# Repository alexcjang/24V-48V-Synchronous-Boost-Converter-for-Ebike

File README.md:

# 24V-48V Synchronous Boost Converter for Ebike

# Synchronous Boost Converter

24V→48V DC-DC converter, 250W rated, 97.51% peak efficiency.

🏆 Won "Most Efficient Design" across all teams in Fall '25 class of Power Electronics Lab.

## Overview
Boost converter designed to power 3 phase electric bike motor, which required conversion from 24-48V. Our team optimized efficiency, winning the category, at the cost of size. This was designed for the Fall '25 class of Power Electronics Lab.

## Key Results
- Peak efficiency: 97.51% at 250W.
- Output ripple: 0.905V
- Efficiency across load range:

## Design
- **Topology:** Synchronous Boost for high efficiency
- **Magnetics:** Custom-wound inductor — 92.16µH, 19 turns, 0.79mm gap, 10 AWG. These specs were chosen using the Kg method on the E cores that were available in the lab, as well as to achieve Vin = 24V, Vout = 48V, ripple = 0.125, and inductor I = 10.417A.
- **Control:** Register-level PWM with dead-time management on TI C2000,
  ADC-based current/voltage sensing
- **PCB:** 4-layer, minimized gating loops and cut ground planes to reduce parasitic capacitance and inductance, seperated sensitive ADC/control signals from high di/dt and high dv/dt areas

## What I'd Change
I would love to have optimized the dead time and switching a bit more. With precise switching, we could have achieved zero voltage switching consistently, which would removes the switching loss from that cycle. We did not have the time to implement this, and also decided that it was too risky as choosing the wrong dead time could result in a short circuit of the switching loop and fry our MOSFETs. If I were to take on this project again outside of the class constraints, I would try different types of cores to allow for a larger inductor which could further increase efficiency and reduce ripple.

## Media

Board 3D model
<br><br><br>

Peak Efficiency Oscilloscope Capture

## Tools
LTSpice, MATLAB, KiCad, TI C2000 (C)

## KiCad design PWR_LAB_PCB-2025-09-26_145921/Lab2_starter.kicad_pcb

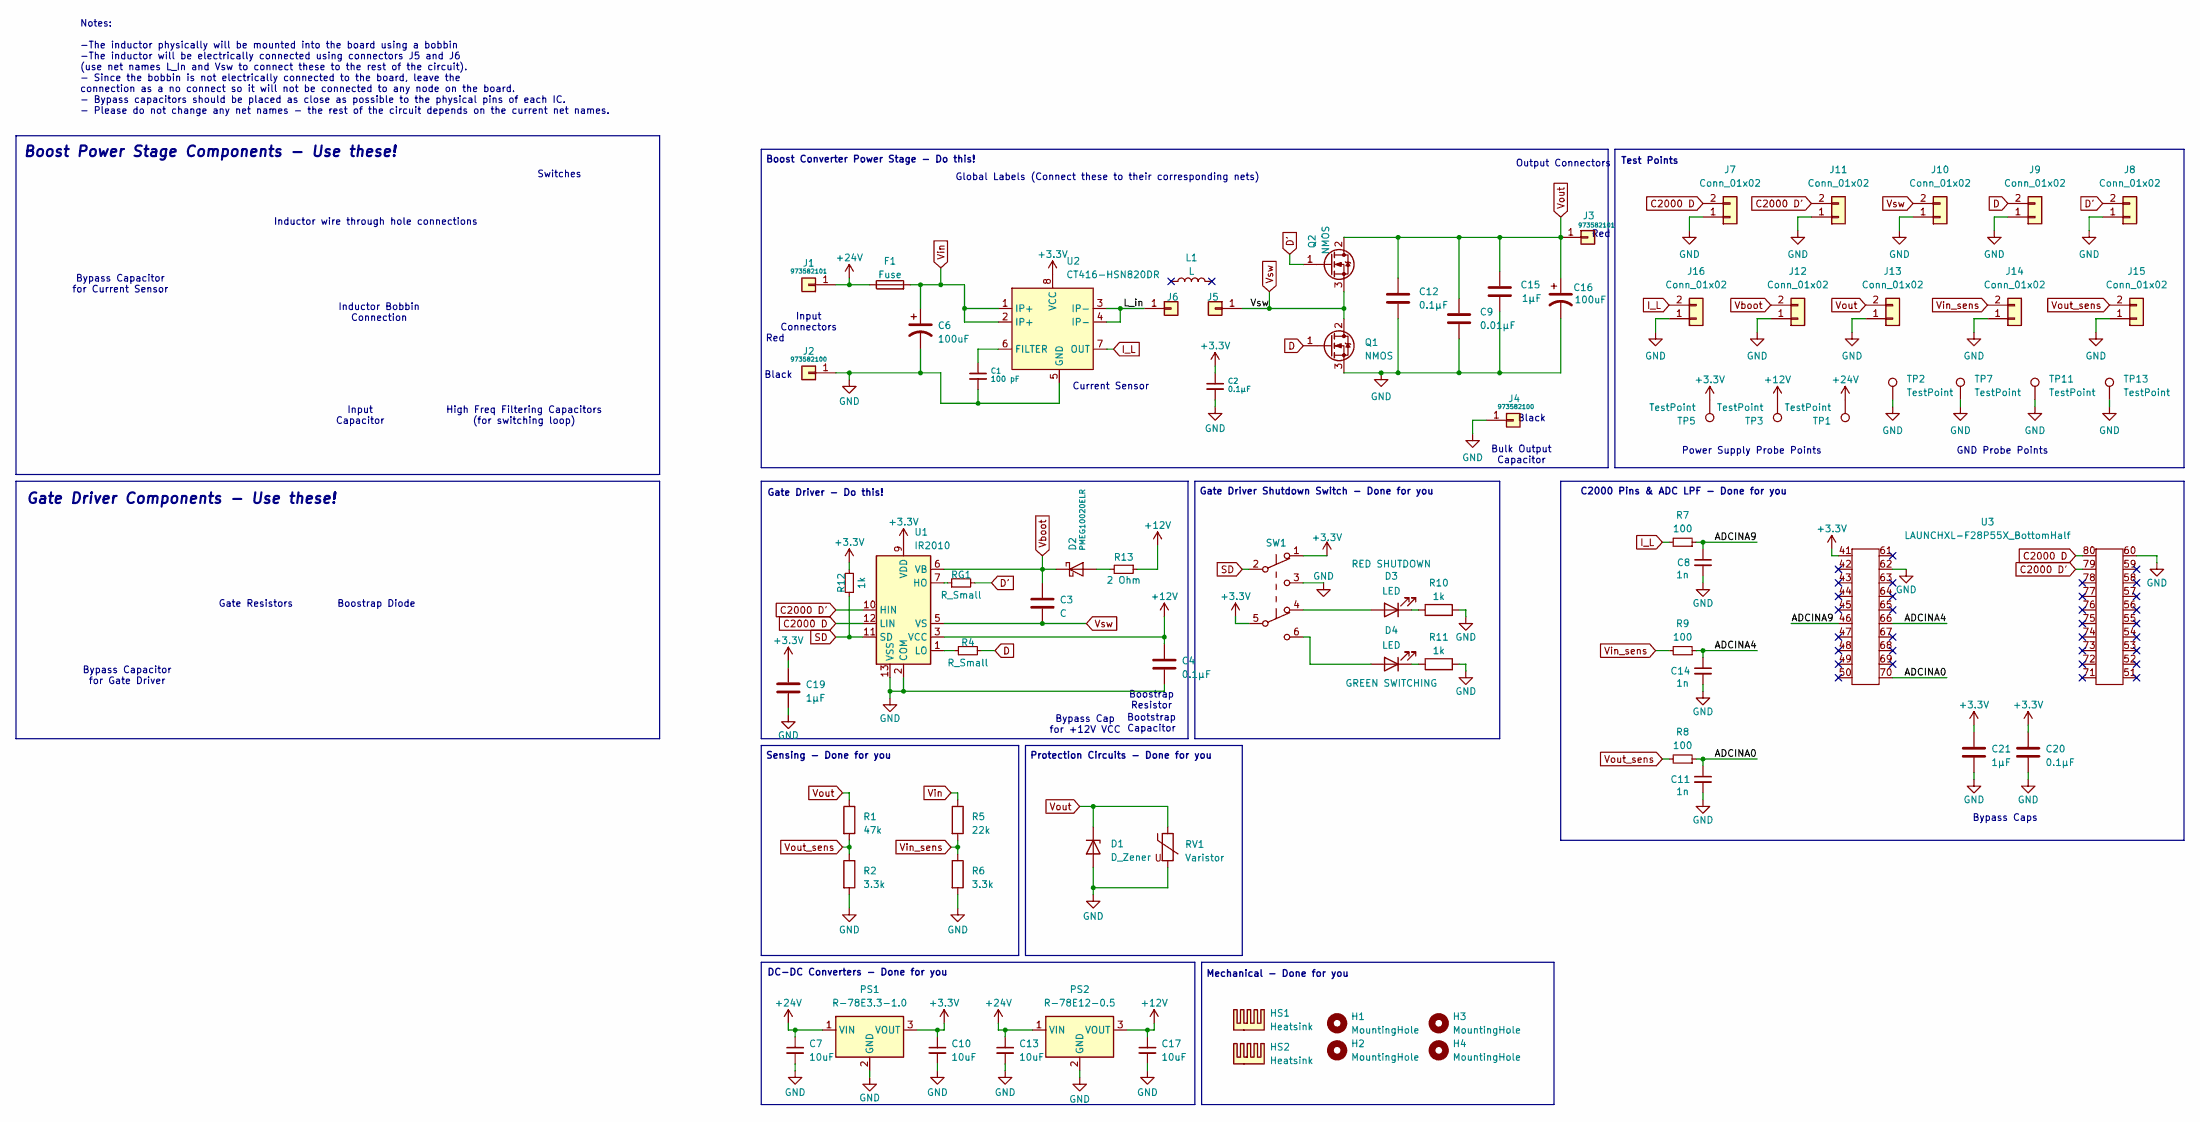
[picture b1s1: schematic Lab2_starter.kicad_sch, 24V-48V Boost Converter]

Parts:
C1: 100 pF; C_0805_2012Metric
C2, C4, C12, C20: 0.1μF; C_0805_2012Metric
C3: C; C_0805_2012Metric
C6, C16: 100uF; 16PX2200MEFC10X20
C7, C10, C13, C17: 10uF; C_0805_2012Metric
C8, C11, C14: 1n; C_0805_2012Metric
C9: 0.01μF; C_0805_2012Metric
C15, C19, C21: 1μF; C_0805_2012Metric
D1: D_Zener; 1.5KE75A
D2: PMEG10020ELR; Nexperia_CFP3_SOD-123W
D3, D4: LED; WL-SMRW_1206_REC
F1: Fuse; 696108003002
H1, H2, H3, H4: MountingHole; MountingHole_3.2mm_M3
HS1, HS2: Heatsink; HSS-B20-NPS-01
J1, J3: 973582101
J2, J4: 973582100
J5, J6: Conn_01x01; Inductor_wire_conn
J7, J8, J9, J10, J11, J12, J13, J14, J15, J16: Conn_01x02; TP
L1: L; Inductor
PS1: R-78E3.3-1.0; PARTREV 6
PS2: R-78E12-0.5; R-78E-0.5_RCP
Q1, Q2: NMOS; TO-220-3_Vertical
R1: 47k; R_0805_2012Metric
R2, R6: 3.3k; R_0805_2012Metric
R4: R_Small; R_0805_2012Metric
R5: 22k; R_0805_2012Metric
R7, R8, R9: 100; R_0805_2012Metric
R10, R11, R12: 1k; R_0805_2012Metric
R13: 2 Ohm; R_0805_2012Metric
RG1: R_Small; R_0805_2012Metric
RV1: Varistor; V100ZA15P
SW1: SW_Push_DPDT; SLW1116297AD
TP1, TP2, TP3, TP5, TP7, TP11, TP13: TestPoint; TestPoint_Loop_D1.80mm_Drill1.0mm_Beaded
U1: IR2010; 1-2199298-3
U2: CT416-HSN820DR; SOIC-8_3.9x4.9mm_P1.27mm
U3: LAUNCHXL-F28P55X_BottomHalf

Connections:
+3.3V: C2.1, C10.1, C19.1, C20.1, C21.1, PS1.3 (VOUT), R12.2, SW1.1 (A), SW1.5 (B), TP5.1, U1.9 (VDD), U2.8 (VCC), U3.41
+12V: C4.1, C17.1, PS2.3 (VOUT), R13.1, TP3.1, U1.3 (VCC)
+24V: C7.1, C13.1, F1.1, J1.1, PS1.1 (VIN), PS2.1 (VIN), TP1.1
/ADCINA0: C11.1, R8.1, U3.70
/ADCINA4: C14.1, R9.1, U3.66
/ADCINA9: C8.1, R7.1, U3.46
/L_in: J6.1, U2.3 (IP-), U2.4 (IP-)
C2000 D: J7.2, U1.12 (LIN), U3.80
C2000 D': J11.2, U1.10 (HIN), U3.79
D: J9.2, Q1.1 (G), R4.2
D': J8.2, Q2.1 (G), RG1.2
GND: C1.2, C2.2, C4.2, C6.2, C7.2, C8.2, C9.2, C10.2, C11.2, C12.2, C13.2, C14.2, C15.2, C16.2, C17.2, C19.2, C20.2, C21.2, D1.2 (A), J2.1, J4.1, J7.1, J8.1, J9.1, J10.1, J11.1, J12.1, J13.1, J14.1, J15.1, J16.1, PS1.2 (GND), PS2.2 (GND), Q1.3 (S), R2.2, R6.2, R10.2, R11.2, RV1.2, SW1.3 (C), TP2.1, TP7.1, TP11.1, TP13.1, U1.2 (COM), U1.13 (VSS), U2.5 (GND), U3.60, U3.62
I_L: J16.2, R7.2, U2.7 (OUT)
unnamed: D2.2 (A), R13.2
unnamed: D3.2 (A), SW1.4 (A)
unnamed: D3.1 (K), R10.1
unnamed: D4.2 (A), SW1.6 (C)
unnamed: D4.1 (K), R11.1
unnamed: RG1.1, U1.7 (HO)
unnamed: R4.1, U1.1 (LO)
unnamed: C1.1, U2.6 (FILTER)
SD: R12.1, SW1.2 (B), U1.11 (SD)
Vboot: C3.1, D2.1 (K), J12.2, U1.6 (VB)
Vin: C6.1, F1.2, R5.1, U2.1 (IP+), U2.2 (IP+)
Vin_sens: J14.2, R5.2, R6.1, R9.2
Vout: C9.1, C12.1, C15.1, C16.1, D1.1 (K), J3.1, J13.2, Q2.2 (D), R1.1, RV1.1
Vout_sens: J15.2, R1.2, R2.1, R8.2
Vsw: C3.2, J5.1, J10.2, Q1.2 (D), Q2.3 (S), U1.5 (VS)

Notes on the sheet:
High Freq Filtering Capacitors (for switching loop)
Black
Inductor wire through hole connections
Input Connectors
Sensing - Done for you
Protection Circuits - Done for you
Input Capacitor
Test Points
Bypass Cap for +12V VCC
Mechanical - Done for you
Red
Power Supply Probe Points
Bootstrap Capacitor
Gate Driver Shutdown Switch - Done for you
Notes: -The inductor physically will be mounted into the board using a bobbin -The inductor will be electrically connected using connectors J5 and J6 (use net names L_In and Vsw to connect these to the rest of the circuit). - Since the bobbin is not electrically connected to the board, leave the co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
Bulk Output Capacitor
Gate Driver - Do this!
Current Sensor
Boostrap Resistor
DC-DC Converters - Done for you
Boost Power Stage Components - Use these!
Gate Resistors
Global Labels (Connect these to their corresponding nets)
C2000 Pins & ADC LPF - Done for you
Boostrap Diode
Output Connectors
Bypass Capacitor for Current Sensor
Inductor Bobbin Connection
Switches
Bypass Capacitor for Gate Driver
Gate Driver Components - Use these!
GND Probe Points
Bypass Caps
Boost Converter Power Stage - Do this!

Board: 4 copper layers, 76 parts (6 on the bottom side), 28 nets, no tracks yet.

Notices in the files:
parts and their libraries:
Copyright 2016 Accelerated Designs. All rights reserved.
